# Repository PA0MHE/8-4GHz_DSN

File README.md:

# 8-4GHz_DSN

8.4 GHz DSN downconverter, intended to use with external LNA (e.g. 25dB Gain, 1dB NF) in front  
Input : 8400 .. 8470 MHz  
Output: 400 .. 470 MHz  
REF-in: 10 MHz  0.7-3.3 Vpp reference input from an OCXO or GPSDO   
Supply: 8V DC  
The converter itself has a conversion gain of around 13dB  

# Key components:

MGA-86576  
BFCN-8450+  
LTC5549  
ADF4351  
ADM7150/1  
ATtiny85-20S  

# PCB

Gerber files are included, PCB's can be ordered at JCL PCB substrate thickness is 0.6mm 

73's Maarten PA0MHE

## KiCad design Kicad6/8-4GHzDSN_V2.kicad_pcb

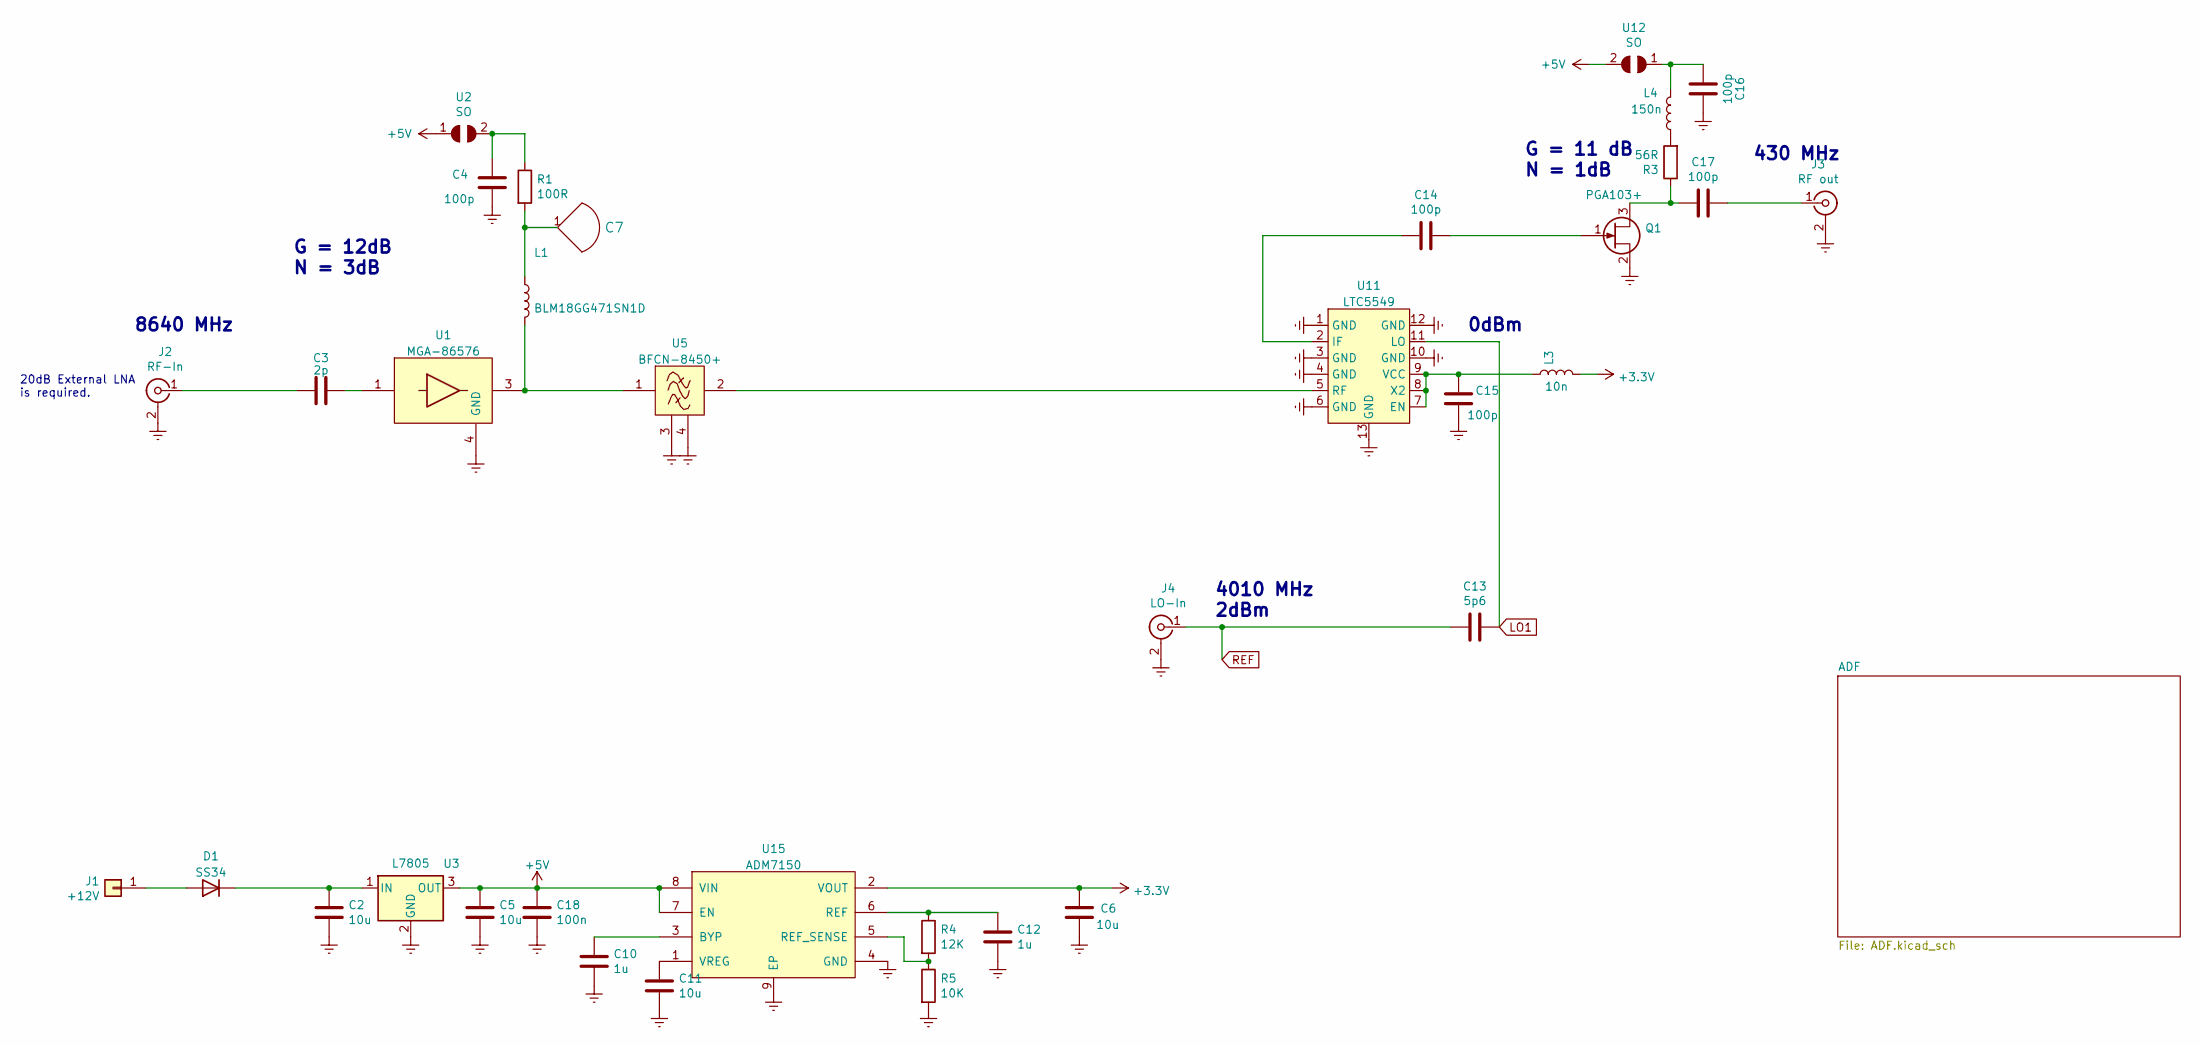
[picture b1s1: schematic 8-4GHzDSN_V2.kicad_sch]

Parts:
C2, C5, C6, C11: 10u; C_0805_2012Metric_Pad1.18x1.45mm_HandSolder
C3: 2p; C_0603_1608Metric_Pad1.08x0.95mm_HandSolder
C4, C15, C16, C17: 100p; C_0603_1608Metric_Pad1.08x0.95mm_HandSolder
C7: printedC; PrintedC
C10, C12: 1u; C_0805_2012Metric_Pad1.18x1.45mm_HandSolder
C13: 5p6; C_0805_2012Metric_Pad1.18x1.45mm_HandSolder
C14: 100p; C_0805_2012Metric_Pad1.18x1.45mm_HandSolder
C18: 100n; C_0805_2012Metric_Pad1.18x1.45mm_HandSolder
D1: SS34; D_SMA
J1: +12V; SolderWirePad_single_SMD_4x5mm
J2: RF-In; SMA_side_PCB
J3: RF out; SMA_side_PCB
J4: LO-In; SMA_side_PCB
L1: BLM18GG471SN1D; L_0201_0603Metric_Pad0.64x0.40mm_HandSolder
L3: 10n; L_0805_2012Metric_Pad1.05x1.20mm_HandSolder
L4: 150n; L_0805_2012Metric_Pad1.15x1.40mm_HandSolder
Q1: PGA103+; SOT-89-3
R1: 100R; R_0805_2012Metric_Pad1.20x1.40mm_HandSolder
R3: 56R; R_0805_2012Metric_Pad1.20x1.40mm_HandSolder
R4: 12K; R_0805_2012Metric_Pad1.20x1.40mm_HandSolder
R5: 10K; R_0805_2012Metric_Pad1.20x1.40mm_HandSolder
U1: MGA-86576
U2, U12: SO; SolderJumper-2_P1.3mm_Open_RoundedPad1.0x1.5mm
U3: L7805; TO-263-3_TabPin2
U5: BFCN-8450+; BFCN-8450
U11: LTC5549; QFN-12-UDB Var A 3.5x2.5mm
U15: ADM7150; SOIC-8-1EP_3.9x4.9mm_P1.27mm_EP2.29x3mm_ThermalVias

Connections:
+3V3: C6.2, L3.2, U15.2 (VOUT); also elsewhere on the board
+5V: C5.2, C18.2, U2.1, U3.3 (OUT), U12.2, U15.7 (EN), U15.8 (VIN)
GNDREF: C2.1, C4.1, C5.1, C6.1, C10.1, C11.1, C12.1, C15.1, C16.1, C18.1, J2.2 (Ext), J3.2 (Ext), J4.2 (Ext), Q1.2 (S), R5.2, U1.2 (GND), U1.4 (GND), U3.2 (GND), U5.3, U5.4, U11.1 (GND), U11.3 (GND), U11.4 (GND), U11.6 (GND), U11.10 (GND), U11.12 (GND), U11.13 (GND), U15.4 (GND), U15.9 (EP); also elsewhere on the board
LO1: C13.2, U11.11 (LO); also elsewhere on the board
unnamed: C2.2, D1.1 (K), U3.1 (IN)
unnamed: C3.1, J2.1 (In)
unnamed: C3.2, U1.1
unnamed: C4.2, R1.1, U2.2
unnamed: C7.1, L1.1, R1.2
unnamed: C10.2, U15.3 (BYP)
unnamed: C11.2, U15.1 (VREG)
unnamed: C12.2, R4.1, U15.6 (REF)
unnamed: C14.1, U11.2 (IF)
unnamed: C14.2, Q1.1 (G)
unnamed: C15.2, L3.1, U11.7 (EN), U11.8 (X2), U11.9 (VCC)
unnamed: C16.2, L4.1, U12.1
unnamed: C17.1, Q1.3 (D), R3.1
unnamed: C17.2, J3.1 (In)
unnamed: D1.2 (A), J1.1
unnamed: L1.2, U1.3, U5.1
unnamed: L4.2, R3.2
unnamed: R4.2, R5.1, U15.5 (REF_SENSE)
unnamed: U5.2, U11.5 (RF)
REF: C13.1, J4.1 (In); also elsewhere on the board

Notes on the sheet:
20dB External LNA is required.
8640 MHz
0dBm
4010 MHz 2dBm
G = 11 dB N = 1dB
G = 12dB N = 3dB
430 MHz

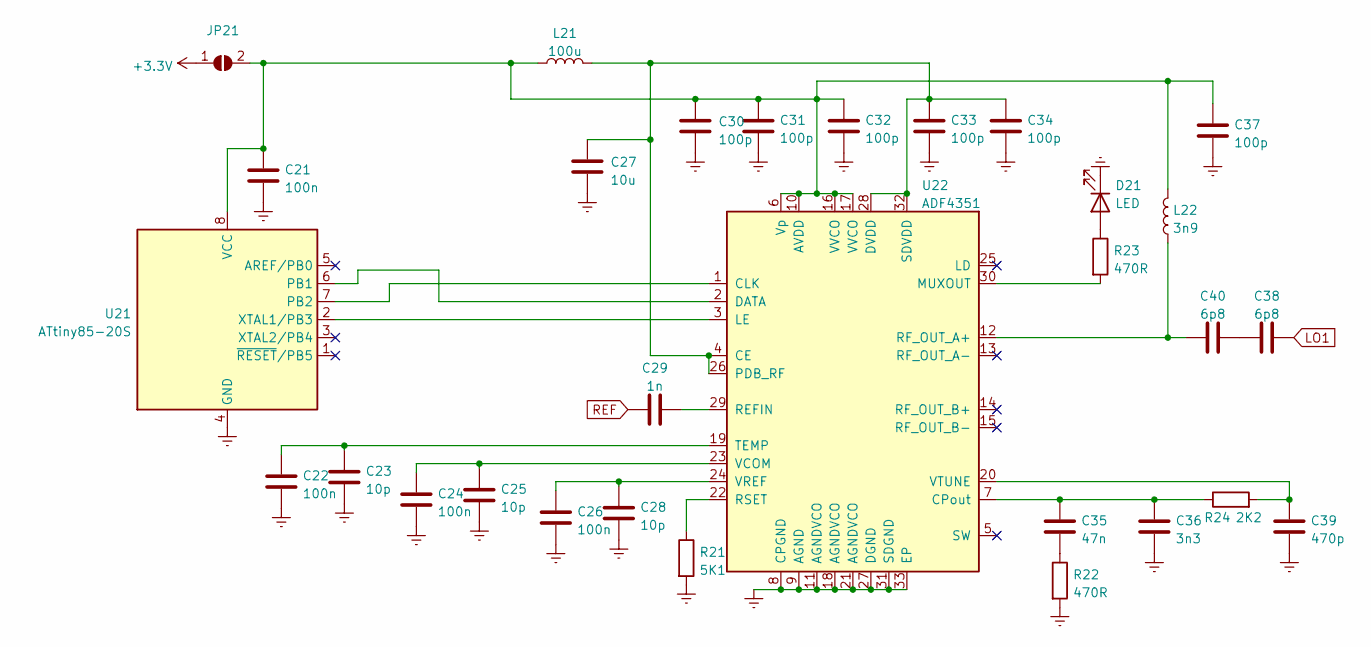
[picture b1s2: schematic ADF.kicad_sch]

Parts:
C21, C22, C24, C26: 100n; C_0805_2012Metric_Pad1.18x1.45mm_HandSolder
C23, C25, C28: 10p; C_0603_1608Metric_Pad1.08x0.95mm_HandSolder
C27: 10u; C_0805_2012Metric_Pad1.18x1.45mm_HandSolder
C29: 1n; C_0805_2012Metric_Pad1.18x1.45mm_HandSolder
C30, C31, C32, C33, C34: 100p; C_0603_1608Metric_Pad1.08x0.95mm_HandSolder
C35: 47n; C_0805_2012Metric_Pad1.18x1.45mm_HandSolder
C36: 3n3; C_0805_2012Metric_Pad1.18x1.45mm_HandSolder
C37: 100p; C_0805_2012Metric_Pad1.18x1.45mm_HandSolder
C38, C40: 6p8; C_0805_2012Metric_Pad1.18x1.45mm_HandSolder
C39: 470p; C_0805_2012Metric_Pad1.18x1.45mm_HandSolder
D21: LED; LED_0805_2012Metric_Pad1.15x1.40mm_HandSolder
JP21: SolderJumper-2_P1.3mm_Open_RoundedPad1.0x1.5mm
L21: 100u; L_0805_2012Metric_Pad1.05x1.20mm_HandSolder
L22: 3n9; L_0805_2012Metric_Pad1.05x1.20mm_HandSolder
R21: 5K1; R_0805_2012Metric_Pad1.20x1.40mm_HandSolder
R22, R23: 470R; R_0805_2012Metric_Pad1.20x1.40mm_HandSolder
R24: 2K2; R_0805_2012Metric_Pad1.20x1.40mm_HandSolder
U21: ATtiny85-20S; SOIC-8W_5.3x5.3mm_P1.27mm
U22: ADF4351; LFCSP-32-1EP_5x5mm_P0.5mm_EP3.6x3.6mm_ThermalVias

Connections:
+3V3: JP21.1 (A); also elsewhere on the board
GNDREF: C21.2, C22.2, C23.2, C24.2, C25.2, C26.2, C27.2, C28.2, C30.2, C31.2, C32.2, C33.2, C34.2, C36.2, C37.2, C39.2, D21.1 (K), R21.2, R22.2, U21.4 (GND), U22.8 (CPGND), U22.9 (AGND), U22.11 (AGNDVCO), U22.18 (AGNDVCO), U22.21 (AGNDVCO), U22.27 (DGND), U22.31 (SDGND), U22.33 (EP); also elsewhere on the board
LO1: C38.2; also elsewhere on the board
unnamed: C21.1, C30.1, C31.1, C32.1, C37.1, JP21.2 (B), L21.1, L22.2, U21.8 (VCC), U22.6 (Vp), U22.10 (AVDD), U22.16 (VVCO), U22.17 (VVCO)
unnamed: C22.1, C23.1, U22.19 (TEMP)
unnamed: C24.1, C25.1, U22.23 (VCOM)
unnamed: C26.1, C28.1, U22.24 (VREF)
unnamed: C27.1, C33.1, C34.1, L21.2, U22.4 (CE), U22.26 (PDB_RF), U22.28 (DVDD), U22.32 (SDVDD)
unnamed: C29.2, U22.29 (REFIN)
unnamed: C35.1, C36.1, R24.1, U22.7 (CPout)
unnamed: C35.2, R22.1
unnamed: C38.1, C40.2
unnamed: C39.1, R24.2, U22.20 (VTUNE)
unnamed: C40.1, L22.1, U22.12 (RF_OUT_A+)
unnamed: D21.2 (A), R23.1
unnamed: R21.1, U22.22 (RSET)
unnamed: R23.2, U22.30 (MUXOUT)
unnamed: U21.2 (XTAL1/PB3), U22.3 (LE)
unnamed: U21.6 (PB1), U22.2 (DATA)
unnamed: U21.7 (PB2), U22.1 (CLK)
REF: C29.1; also elsewhere on the board

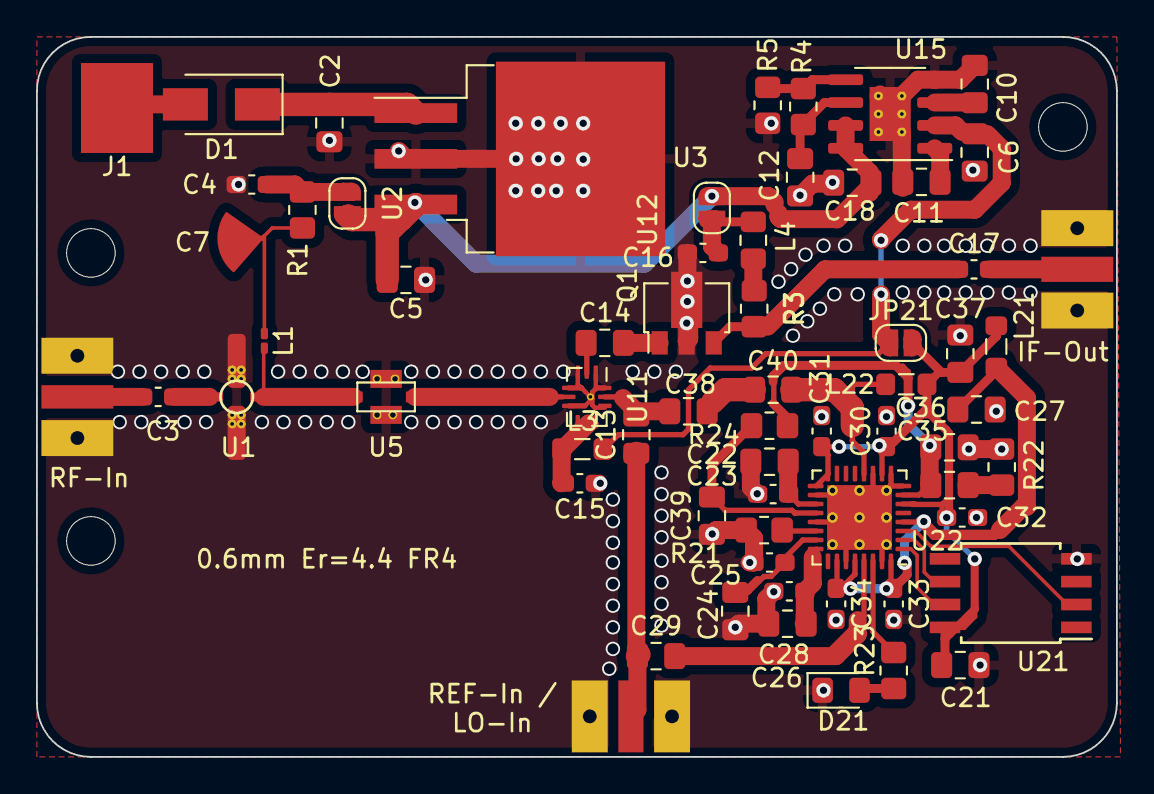
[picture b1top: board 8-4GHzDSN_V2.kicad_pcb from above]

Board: 2 copper layers, 60.0 x 40.0 mm, 65 parts (0 on the bottom side), 41 nets.

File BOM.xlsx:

Reference | Quantity | Value | Footprint | Datasheet
C10 C12 | 2 | 1u | Capacitor_SMD:C_0805_2012Metric_Pad1.18x1.45mm_HandSolder
C13 | 1 | 5p6 | Capacitor_SMD:C_0805_2012Metric_Pad1.18x1.45mm_HandSolder
C14 C37 | 2 | 100p | Capacitor_SMD:C_0805_2012Metric_Pad1.18x1.45mm_HandSolder
C18 C21 C22 C24 C26 | 5 | 100n | Capacitor_SMD:C_0805_2012Metric_Pad1.18x1.45mm_HandSolder
C2 C5 C6 C11 C27 | 5 | 10u | Capacitor_SMD:C_0805_2012Metric_Pad1.18x1.45mm_HandSolder
C23 C25 C28 | 3 | 10p | Capacitor_SMD:C_0603_1608Metric_Pad1.08x0.95mm_HandSolder
C29 | 1 | 1n | Capacitor_SMD:C_0805_2012Metric_Pad1.18x1.45mm_HandSolder
C3 | 1 | 2p | Capacitor_SMD:C_0603_1608Metric_Pad1.08x0.95mm_HandSolder
C35 | 1 | 47n | Capacitor_SMD:C_0805_2012Metric_Pad1.18x1.45mm_HandSolder
C36 | 1 | 3n3 | Capacitor_SMD:C_0805_2012Metric_Pad1.18x1.45mm_HandSolder
C38 C40 | 2 | 6p8 | Capacitor_SMD:C_0805_2012Metric_Pad1.18x1.45mm_HandSolder
C39 | 1 | 470p | Capacitor_SMD:C_0805_2012Metric_Pad1.18x1.45mm_HandSolder
C4 C15 C16 C17 C30 C31 C32 C33 C34 | 9 | 100p | Capacitor_SMD:C_0603_1608Metric_Pad1.08x0.95mm_HandSolder
C7 | 1 | printedC | Maarten_Kicad6:PrintedC
D1 | 1 | SS34 | Diode_SMD:D_SMA
D21 | 1 | LED | LED_SMD:LED_0805_2012Metric_Pad1.15x1.40mm_HandSolder
J1 | 1 | +12V | Maarten_Kicad6:SolderWirePad_single_SMD_4x5mm
J2 | 1 | RF-In | Maarten_Kicad6:SMA_side_PCB
J3 | 1 | RF out | Maarten_Kicad6:SMA_side_PCB
J4 | 1 | LO-In | Maarten_Kicad6:SMA_side_PCB
JP21 | 1 | ~ | Jumper:SolderJumper-2_P1.3mm_Open_RoundedPad1.0x1.5mm
L1 | 1 | BLM18GG471SN1D | Inductor_SMD:L_0201_0603Metric_Pad0.64x0.40mm_HandSolder
L21 | 1 | 100u | Inductor_SMD:L_0805_2012Metric_Pad1.05x1.20mm_HandSolder
L22 | 1 | 3n9 | Inductor_SMD:L_0805_2012Metric_Pad1.05x1.20mm_HandSolder
L3 | 1 | 10n | Inductor_SMD:L_0805_2012Metric_Pad1.05x1.20mm_HandSolder
L4 | 1 | 150n | Inductor_SMD:L_0805_2012Metric_Pad1.15x1.40mm_HandSolder
Q1 | 1 | PGA103+ | Package_TO_SOT_SMD:SOT-89-3
R1 | 1 | 100R | Resistor_SMD:R_0805_2012Metric_Pad1.20x1.40mm_HandSolder
R21 | 1 | 5K1 | Resistor_SMD:R_0805_2012Metric_Pad1.20x1.40mm_HandSolder
R22 R23 | 2 | 470R | Resistor_SMD:R_0805_2012Metric_Pad1.20x1.40mm_HandSolder
R24 | 1 | 2K2 | Resistor_SMD:R_0805_2012Metric_Pad1.20x1.40mm_HandSolder
R3 | 1 | 56R | Resistor_SMD:R_0805_2012Metric_Pad1.20x1.40mm_HandSolder
R4 | 1 | 12K | Resistor_SMD:R_0805_2012Metric_Pad1.20x1.40mm_HandSolder
R5 | 1 | 10K | Resistor_SMD:R_0805_2012Metric_Pad1.20x1.40mm_HandSolder
U1 | 1 | MGA-86576 | Maarten_Kicad6:MGA-86576
U11 | 1 | LTC5549 | Maarten_Kicad6:QFN-12-UDB Var A 3.5x2.5mm
U15 | 1 | ADM7150 | Package_SO:SOIC-8-1EP_3.9x4.9mm_P1.27mm_EP2.29x3mm_ThermalVias
U2 U12 | 2 | SO | Jumper:SolderJumper-2_P1.3mm_Open_RoundedPad1.0x1.5mm
U21 | 1 | ATtiny85-20S | Package_SO:SOIC-8W_5.3x5.3mm_P1.27mm | http://ww1.microchip.com/downloads/en/DeviceDoc/atmel-2586-a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
U22 | 1 | ADF4351 | Package_CSP:LFCSP-32-1EP_5x5mm_P0.5mm_EP3.6x3.6mm_ThermalVias | https://www.analog.com/media/en/technical-documentation/data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
U3 | 1 | L7805 | Package_TO_SOT_SMD:TO-263-3_TabPin2 | http://www.st.com/content/ccc/resource/technical/document/da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
U5 | 1 | BFCN-8450+ | Maarten_Kicad6:BFCN-8450

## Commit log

2022-09-18 Added files
